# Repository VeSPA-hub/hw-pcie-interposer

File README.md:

# PCIe interposer

Board design files of the VeSPA PCIe interposer

	Note: This design was performed in KiCad nightly , you will need a Nightly build to open and edit these source files.

# Status

This version has not been fully tested yet.

# What it is

This board can tap PCIe signals (RX, TX and clock) at Gen2 speed.
Signals go to a redriver before they are sent to the actual analyzer using a DisplayPort cable.

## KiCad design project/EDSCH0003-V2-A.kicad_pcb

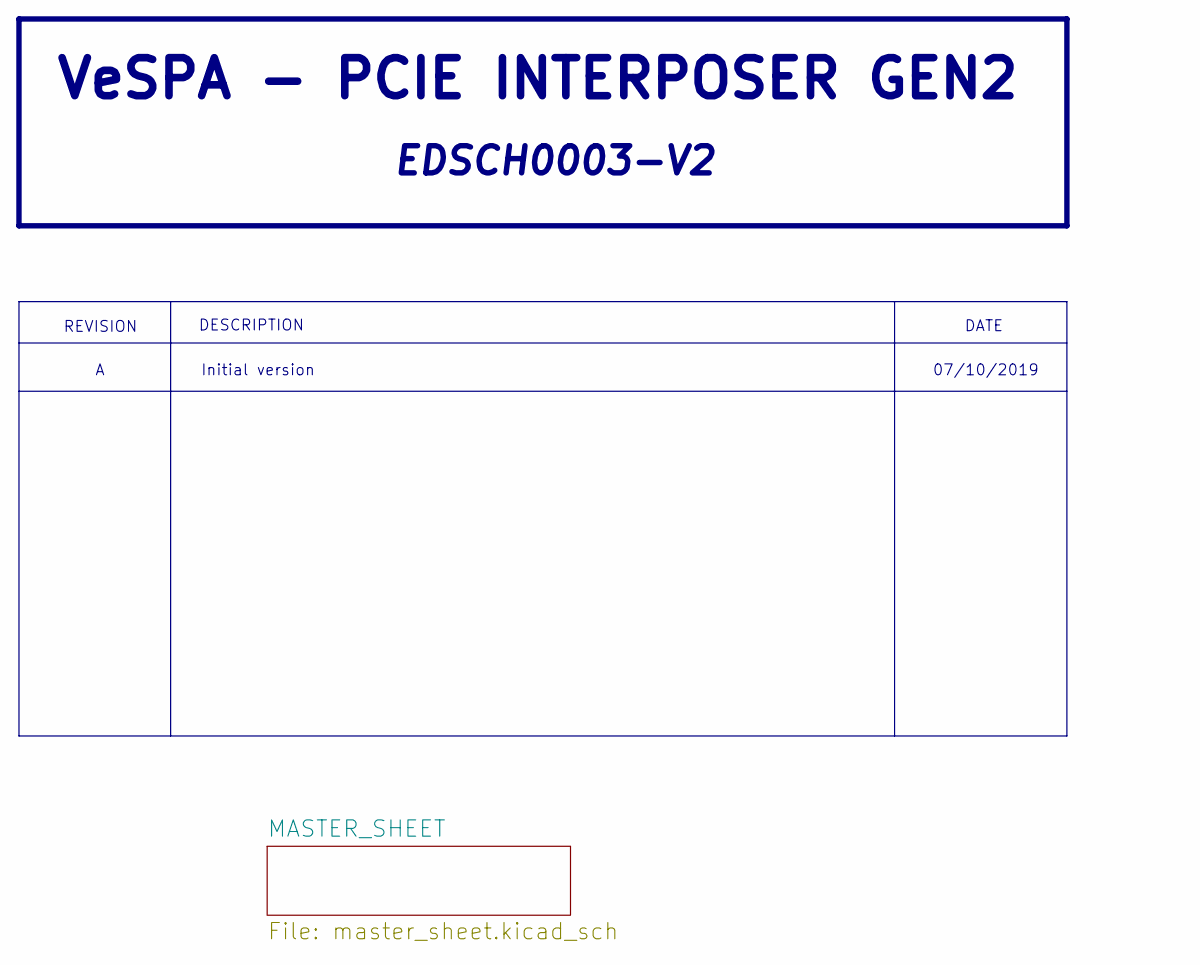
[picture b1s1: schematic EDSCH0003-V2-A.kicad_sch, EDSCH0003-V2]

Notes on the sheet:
VeSPA - PCIE INTERPOSER GEN2
REVISION
DESCRIPTION
Initial version
EDSCH0003-V2
DATE
07/10/2019

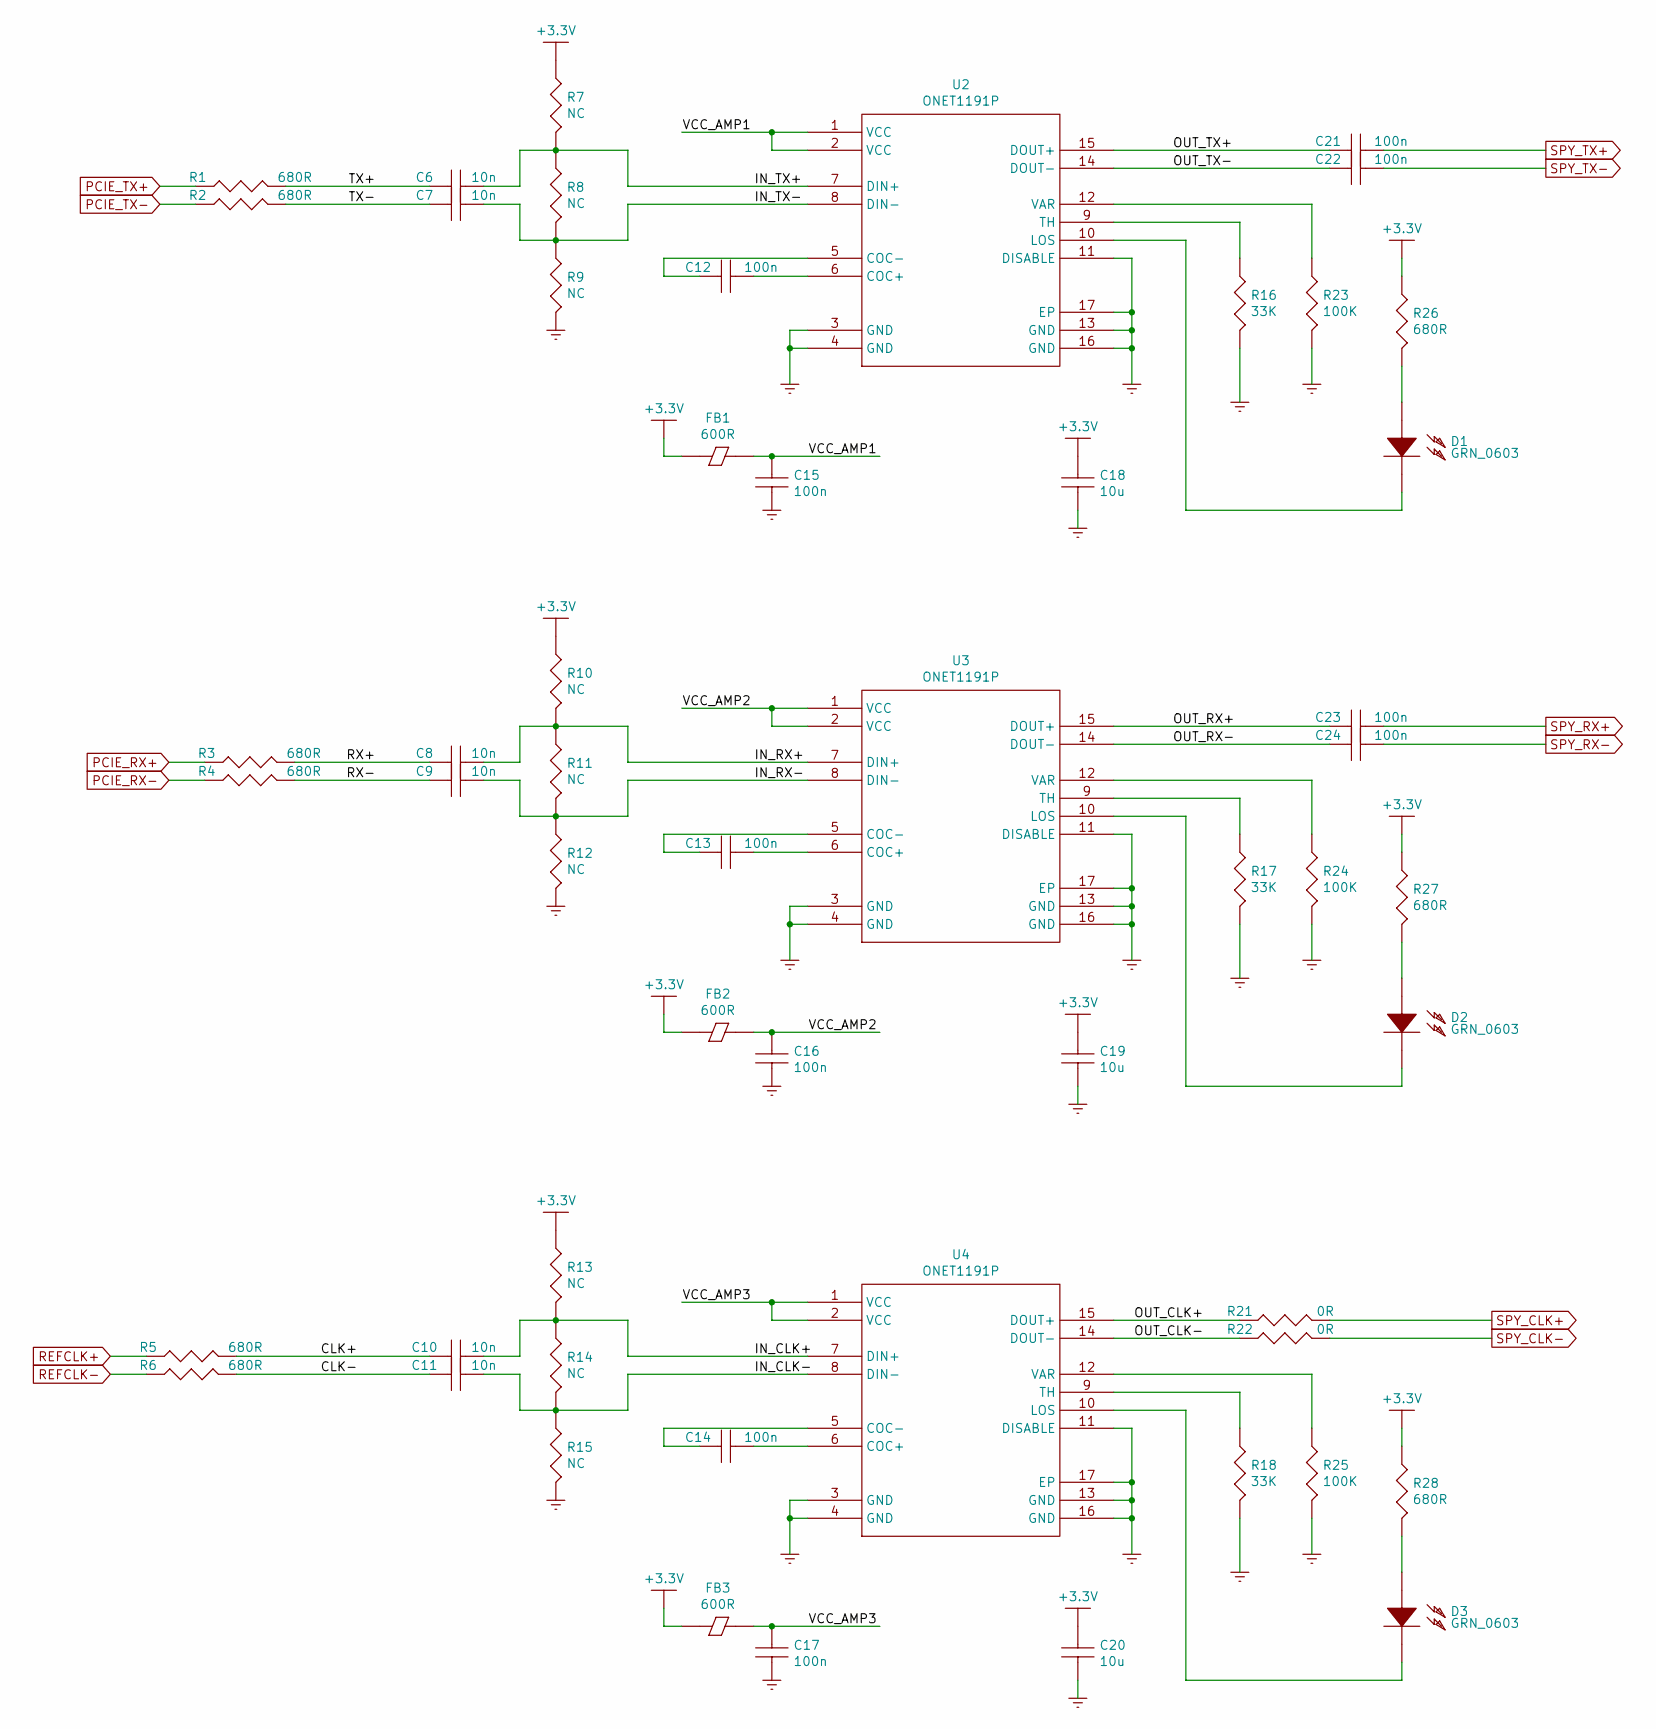
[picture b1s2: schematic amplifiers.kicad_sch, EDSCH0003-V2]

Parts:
C6, C7, C8, C9, C10, C11: C10N_0402; r_smt0402_ref
C12, C13, C14, C15, C16, C17, C21, C22, C23, C24: C100N_16V_0402; r_smt0402_ref
C18, C19, C20: C10U_50V_1206; c_smt1206_ref
D1, D2, D3: LED_GRN_0603; LED_0603_1608Metric_Castellated
FB1, FB2, FB3: FR_600R_0.2A_0402; r_smt0402_ref
R1, R2, R3, R4, R5, R6, R26, R27, R28: R680R_1%_0603; r_smt0603_ref
R7, R8, R9, R10, R11, R12, R13, R14, R15: R_NC_0402; r_smt0402_ref
R16, R17, R18: R33K_1%_0402; r_smt0402_ref
R21, R22: R0R_5%_0402; r_smt0402_ref
R23, R24, R25: R100K_1%_0402; r_smt0402_ref
U2, U3, U4: ONET1191P; QFN-16-1EP_3x3mm_P0.5mm_EP1.7x1.7mm

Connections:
+3.3V: C18.1, C19.1, C20.1, FB1.1, FB2.1, FB3.1, R7.1, R10.1, R13.1, R26.1, R27.1, R28.1; also elsewhere on the board
/MASTER_SHEET/AMPLIFIERS/CLK+: C10.1, R5.2
/MASTER_SHEET/AMPLIFIERS/CLK-: C11.1, R6.2
/MASTER_SHEET/AMPLIFIERS/IN_CLK+: C10.2, R13.2, R14.1, U4.7 (DIN+)
/MASTER_SHEET/AMPLIFIERS/IN_CLK-: C11.2, R14.2, R15.1, U4.8 (DIN-)
/MASTER_SHEET/AMPLIFIERS/IN_RX+: C8.2, R10.2, R11.1, U3.7 (DIN+)
/MASTER_SHEET/AMPLIFIERS/IN_RX-: C9.2, R11.2, R12.1, U3.8 (DIN-)
/MASTER_SHEET/AMPLIFIERS/IN_TX+: C6.2, R7.2, R8.1, U2.7 (DIN+)
/MASTER_SHEET/AMPLIFIERS/IN_TX-: C7.2, R8.2, R9.1, U2.8 (DIN-)
/MASTER_SHEET/AMPLIFIERS/OUT_CLK+: R21.1, U4.15 (DOUT+)
/MASTER_SHEET/AMPLIFIERS/OUT_CLK-: R22.1, U4.14 (DOUT-)
/MASTER_SHEET/AMPLIFIERS/OUT_RX+: C23.1, U3.15 (DOUT+)
/MASTER_SHEET/AMPLIFIERS/OUT_RX-: C24.1, U3.14 (DOUT-)
/MASTER_SHEET/AMPLIFIERS/OUT_TX+: C21.1, U2.15 (DOUT+)
/MASTER_SHEET/AMPLIFIERS/OUT_TX-: C22.1, U2.14 (DOUT-)
/MASTER_SHEET/AMPLIFIERS/RX+: C8.1, R3.2
/MASTER_SHEET/AMPLIFIERS/RX-: C9.1, R4.2
/MASTER_SHEET/AMPLIFIERS/TX+: C6.1, R1.2
/MASTER_SHEET/AMPLIFIERS/TX-: C7.1, R2.2
/MASTER_SHEET/AMPLIFIERS/VCC_AMP1: C15.1, FB1.2, U2.1 (VCC), U2.2 (VCC)
/MASTER_SHEET/AMPLIFIERS/VCC_AMP2: C16.1, FB2.2, U3.1 (VCC), U3.2 (VCC)
/MASTER_SHEET/AMPLIFIERS/VCC_AMP3: C17.1, FB3.2, U4.1 (VCC), U4.2 (VCC)
GND: C15.2, C16.2, C17.2, C18.2, C19.2, C20.2, R9.2, R12.2, R15.2, R16.2, R17.2, R18.2, R23.2, R24.2, R25.2, U2.3 (GND), U2.4 (GND), U2.11 (DISABLE), U2.13 (GND), U2.16 (GND), U2.17 (EP), U3.3 (GND), U3.4 (GND), U3.11 (DISABLE), U3.13 (GND), U3.16 (GND), U3.17 (EP), U4.3 (GND), U4.4 (GND), U4.11 (DISABLE), U4.13 (GND), U4.16 (GND), U4.17 (EP); also elsewhere on the board
unnamed: C12.1, U2.5 (COC-)
unnamed: C12.2, U2.6 (COC+)
unnamed: C13.1, U3.5 (COC-)
unnamed: C13.2, U3.6 (COC+)
unnamed: C14.1, U4.5 (COC-)
unnamed: C14.2, U4.6 (COC+)
unnamed: D1.1 (A), R26.2
unnamed: D1.2 (K), U2.10 (LOS)
unnamed: D2.1 (A), R27.2
unnamed: D2.2 (K), U3.10 (LOS)
unnamed: D3.1 (A), R28.2
unnamed: D3.2 (K), U4.10 (LOS)
unnamed: R16.1, U2.9 (TH)
unnamed: R17.1, U3.9 (TH)
unnamed: R18.1, U4.9 (TH)
unnamed: R23.1, U2.12 (VAR)
unnamed: R24.1, U3.12 (VAR)
unnamed: R25.1, U4.12 (VAR)
PCIE_RX+: R3.1; also elsewhere on the board
PCIE_RX-: R4.1; also elsewhere on the board
PCIE_TX+: R1.1; also elsewhere on the board
PCIE_TX-: R2.1; also elsewhere on the board
REFCLK+: R5.1; also elsewhere on the board
REFCLK-: R6.1; also elsewhere on the board
SPY_CLK+: R21.2; also elsewhere on the board
SPY_CLK-: R22.2; also elsewhere on the board
SPY_RX+: C23.2; also elsewhere on the board
SPY_RX-: C24.2; also elsewhere on the board
SPY_TX+: C21.2; also elsewhere on the board
SPY_TX-: C22.2; also elsewhere on the board

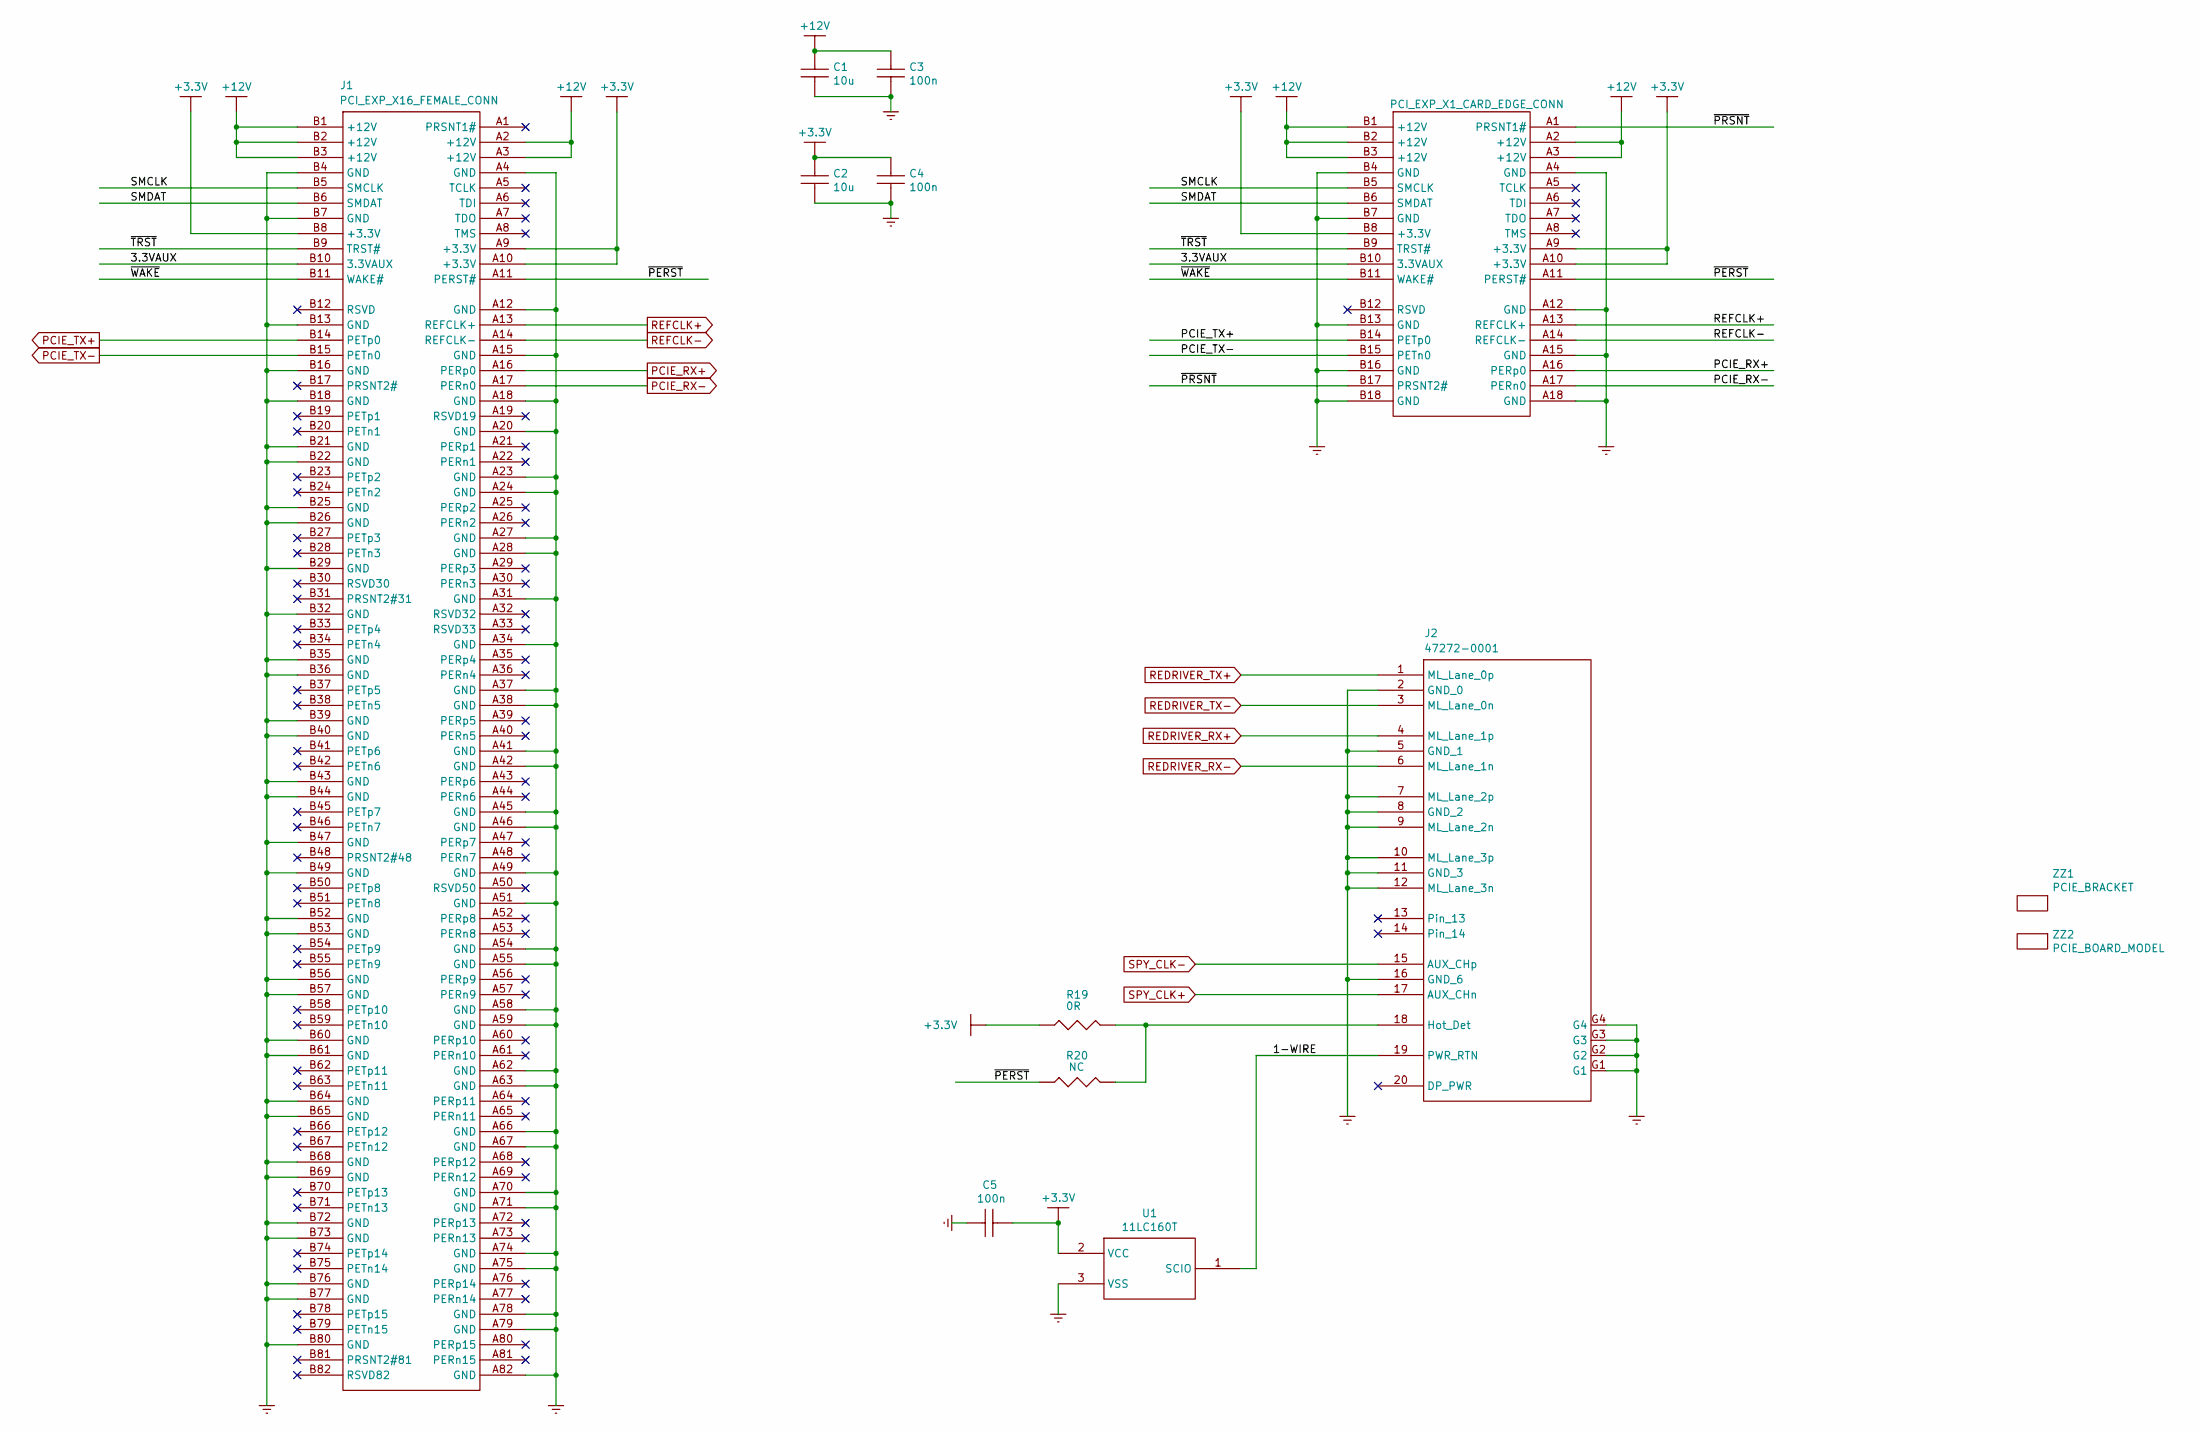
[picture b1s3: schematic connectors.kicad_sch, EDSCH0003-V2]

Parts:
C1, C2: C10U_50V_1206; c_smt1206_ref
C3, C4, C5: C100N_16V_0402; r_smt0402_ref
J1: PCIEXP_X16_EDGE_MOUNT_CONN; samtec_pcie_ems2
J2: DISPLAY_PORT; molex_display_port
P1: PCIEXP_X1_CARD_EDGE; BUS_PCIexpress_x1
R19: R0R_5%_0402; r_smt0402_ref
R20: R_NC_0402; r_smt0402_ref
U1: EEPROM_1WIRE_2Kx8_11LC160T; SOT-23
ZZ1: PCIE_BRACKET; pcie_bracket
ZZ2: PCIE_BOARD_MODEL; BUS_PCIexpress

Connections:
+3.3V: C2.1, C4.1, C5.2, J1.A9 (+3.3V), J1.A10 (+3.3V), J1.B8 (+3.3V), P1.A9 (+3.3V), P1.A10 (+3.3V), P1.B8 (+3.3V), R19.1, U1.2 (VCC); also elsewhere on the board
+12V: C1.1, C3.1, J1.A2 (+12V), J1.A3 (+12V), J1.B1 (+12V), J1.B2 (+12V), J1.B3 (+12V), P1.A2 (+12V), P1.A3 (+12V), P1.B1 (+12V), P1.B2 (+12V), P1.B3 (+12V)
/MASTER_SHEET/CONNECTORS/1-WIRE: J2.19 (PWR_RTN), U1.1 (SCIO)
/MASTER_SHEET/CONNECTORS/3.3VAUX: J1.B10 (3.3VAUX), P1.B10 (3.3VAUX)
/MASTER_SHEET/CONNECTORS/SMCLK: J1.B5 (SMCLK), P1.B5 (SMCLK)
/MASTER_SHEET/CONNECTORS/SMDAT: J1.B6 (SMDAT), P1.B6 (SMDAT)
/MASTER_SHEET/CONNECTORS/~PERST: J1.A11 (PERST#), P1.A11 (PERST#), R20.1
/MASTER_SHEET/CONNECTORS/~PRSNT: P1.A1 (PRSNT1#), P1.B17 (PRSNT2#)
/MASTER_SHEET/CONNECTORS/~TRST: J1.B9 (TRST#), P1.B9 (TRST#)
/MASTER_SHEET/CONNECTORS/~WAKE: J1.B11 (WAKE#), P1.B11 (WAKE#)
GND: C1.2, C2.2, C3.2, C4.2, C5.1, J1.A4 (GND), J1.A12 (GND), J1.A15 (GND), J1.A18 (GND), J1.A20 (GND), J1.A23 (GND), J1.A24 (GND), J1.A27 (GND), J1.A28 (GND), J1.A31 (GND), J1.A34 (GND), J1.A37 (GND), J1.A38 (GND), J1.A41 (GND), J1.A42 (GND), J1.A45 (GND), J1.A46 (GND), J1.A49 (GND), J1.A51 (GND), J1.A54 (GND), J1.A55 (GND), J1.A58 (GND), J1.A59 (GND), J1.A62 (GND), J1.A63 (GND), J1.A66 (GND), J1.A67 (GND), J1.A70 (GND), J1.A71 (GND), J1.A74 (GND), J1.A75 (GND), J1.A78 (GND), J1.A79 (GND), J1.A82 (GND), J1.B4 (GND), J1.B7 (GND), J1.B13 (GND), J1.B16 (GND), J1.B18 (GND), J1.B21 (GND), J1.B22 (GND), J1.B25 (GND), J1.B26 (GND), J1.B29 (GND), J1.B32 (GND), J1.B35 (GND), J1.B36 (GND), J1.B39 (GND), J1.B40 (GND), J1.B43 (GND), J1.B44 (GND), J1.B47 (GND), J1.B49 (GND), J1.B52 (GND), J1.B53 (GND), J1.B56 (GND), J1.B57 (GND), J1.B60 (GND), J1.B61 (GND), J1.B64 (GND), J1.B65 (GND), J1.B68 (GND), J1.B69 (GND), J1.B72 (GND), J1.B73 (GND), J1.B76 (GND), J1.B77 (GND), J1.B80 (GND), J2.2 (GND_0), J2.5 (GND_1), J2.7 (ML_Lane_2p), J2.8 (GND_2), J2.9 (ML_Lane_2n), J2.10 (ML_Lane_3p), J2.11 (GND_3), J2.12 (ML_Lane_3n), J2.16 (GND_6), J2.G1, J2.G2, J2.G3, J2.G4, P1.A4 (GND), P1.A12 (GND), P1.A15 (GND), P1.A18 (GND), P1.B4 (GND), P1.B7 (GND), P1.B13 (GND), P1.B16 (GND), P1.B18 (GND), U1.3 (VSS); also elsewhere on the board
unnamed: J2.18 (Hot_Det), R19.2, R20.2
PCIE_RX+: J1.A16 (PERp0), P1.A16 (PERp0); also elsewhere on the board
PCIE_RX-: J1.A17 (PERn0), P1.A17 (PERn0); also elsewhere on the board
PCIE_TX+: J1.B14 (PETp0), P1.B14 (PETp0); also elsewhere on the board
PCIE_TX-: J1.B15 (PETn0), P1.B15 (PETn0); also elsewhere on the board
REDRIVER_RX+: J2.4 (ML_Lane_1p); also elsewhere on the board
REDRIVER_RX-: J2.6 (ML_Lane_1n); also elsewhere on the board
REDRIVER_TX+: J2.1 (ML_Lane_0p); also elsewhere on the board
REDRIVER_TX-: J2.3 (ML_Lane_0n); also elsewhere on the board
REFCLK+: J1.A13 (REFCLK+), P1.A13 (REFCLK+); also elsewhere on the board
REFCLK-: J1.A14 (REFCLK-), P1.A14 (REFCLK-); also elsewhere on the board
SPY_CLK+: J2.17 (AUX_CHn); also elsewhere on the board
SPY_CLK-: J2.15 (AUX_CHp); also elsewhere on the board

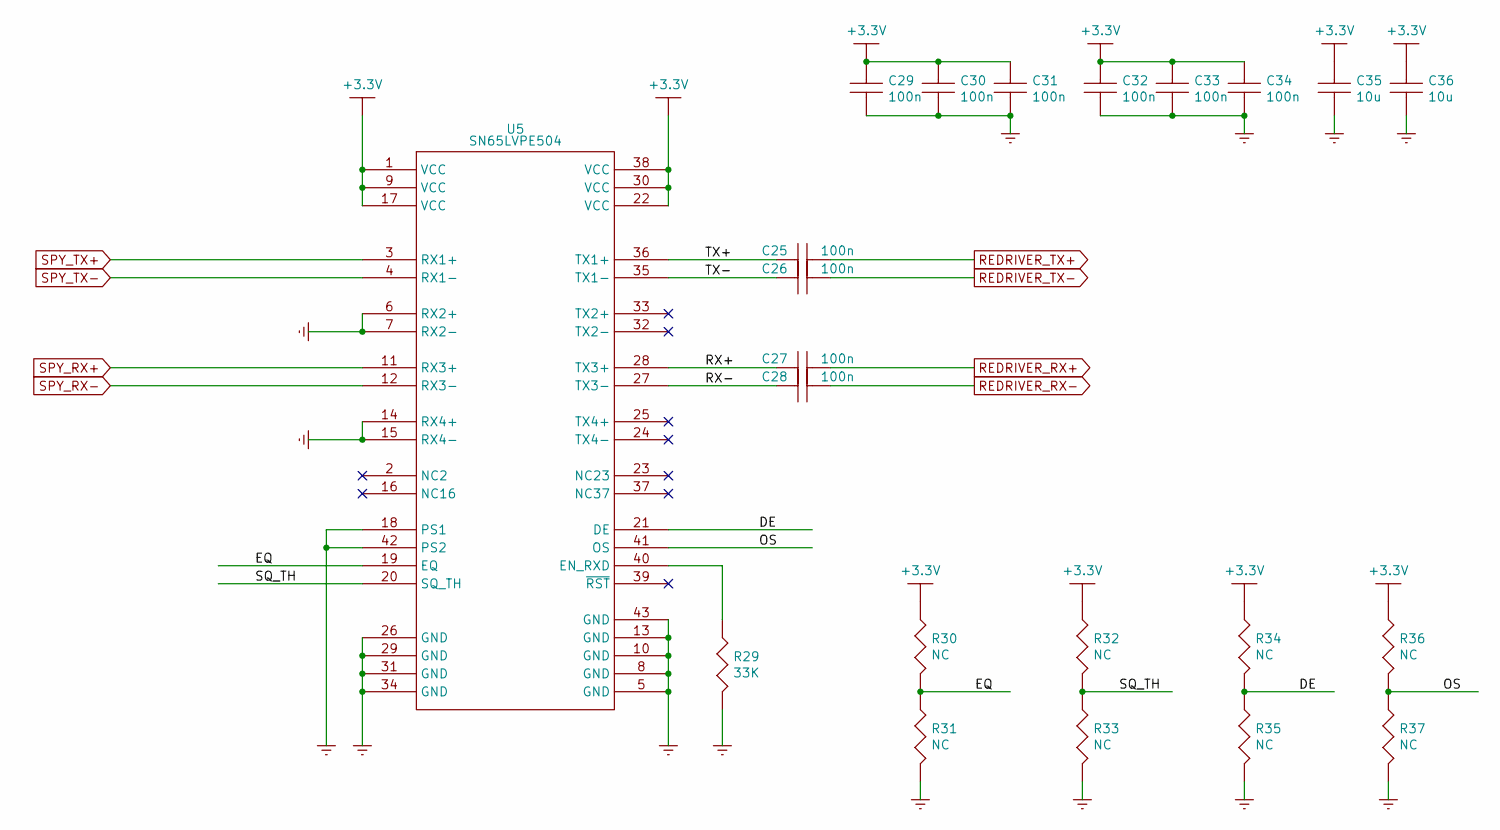
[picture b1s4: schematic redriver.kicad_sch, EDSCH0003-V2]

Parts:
C25, C26, C27, C28, C29, C30, C31, C32, C33, C34: C100N_16V_0402; r_smt0402_ref
C35, C36: C10U_50V_1206; c_smt1206_ref
R29: R33K_1%_0402; r_smt0402_ref
R30, R31, R32, R33, R34, R35, R36, R37: R_NC_0402; r_smt0402_ref
U5: PCIe_HALF_x4_Gen2_SN65LVPE504; pwqfn-n42

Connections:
+3.3V: C29.1, C30.1, C31.1, C32.1, C33.1, C34.1, C35.1, C36.1, R30.1, R32.1, R34.1, R36.1, U5.1 (VCC), U5.9 (VCC), U5.17 (VCC), U5.22 (VCC), U5.30 (VCC), U5.38 (VCC); also elsewhere on the board
/MASTER_SHEET/REDRIVER/DE: R34.2, R35.1, U5.21 (DE)
/MASTER_SHEET/REDRIVER/EQ: R30.2, R31.1, U5.19 (EQ)
/MASTER_SHEET/REDRIVER/OS: R36.2, R37.1, U5.41 (OS)
/MASTER_SHEET/REDRIVER/RX+: C27.1, U5.28 (TX3+)
/MASTER_SHEET/REDRIVER/RX-: C28.1, U5.27 (TX3-)
/MASTER_SHEET/REDRIVER/SQ_TH: R32.2, R33.1, U5.20 (SQ_TH)
/MASTER_SHEET/REDRIVER/TX+: C25.1, U5.36 (TX1+)
/MASTER_SHEET/REDRIVER/TX-: C26.1, U5.35 (TX1-)
GND: C29.2, C30.2, C31.2, C32.2, C33.2, C34.2, C35.2, C36.2, R29.2, R31.2, R33.2, R35.2, R37.2, U5.5 (GND), U5.6 (RX2+), U5.7 (RX2-), U5.8 (GND), U5.10 (GND), U5.13 (GND), U5.14 (RX4+), U5.15 (RX4-), U5.18 (PS1), U5.26 (GND), U5.29 (GND), U5.31 (GND), U5.34 (GND), U5.42 (PS2), U5.43 (GND); also elsewhere on the board
unnamed: R29.1, U5.40 (EN_RXD)
REDRIVER_RX+: C27.2; also elsewhere on the board
REDRIVER_RX-: C28.2; also elsewhere on the board
REDRIVER_TX+: C25.2; also elsewhere on the board
REDRIVER_TX-: C26.2; also elsewhere on the board
SPY_RX+: U5.11 (RX3+); also elsewhere on the board
SPY_RX-: U5.12 (RX3-); also elsewhere on the board
SPY_TX+: U5.3 (RX1+); also elsewhere on the board
SPY_TX-: U5.4 (RX1-); also elsewhere on the board

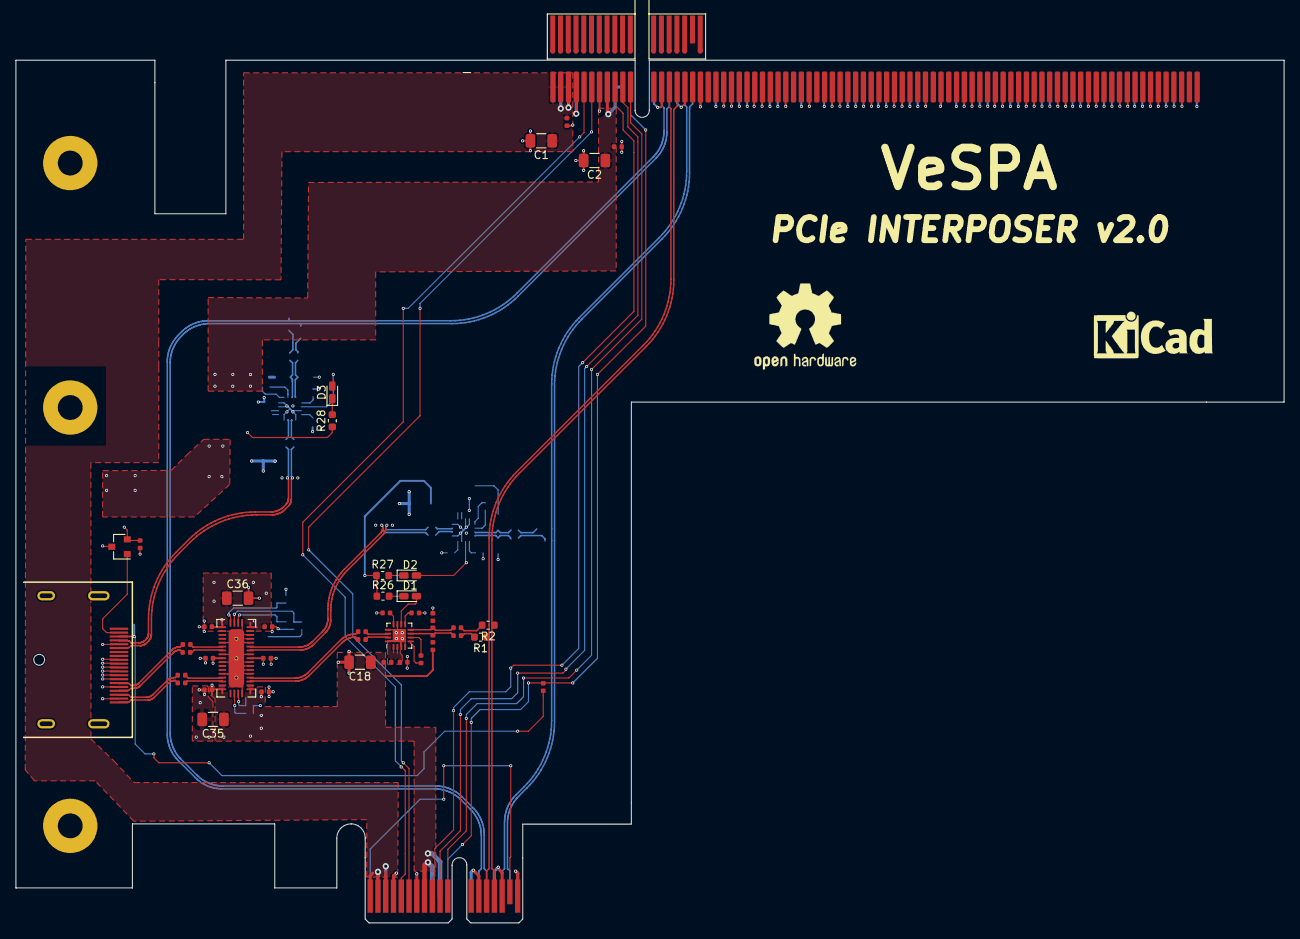
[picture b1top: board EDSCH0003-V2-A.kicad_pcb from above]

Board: 4 copper layers, 163.4 x 111.2 mm, 89 parts (0 on the bottom side), 76 nets.

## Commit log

2020-07-30 Initial release
2020-08-21 Clean-up files
2020-08-21 Add gerber files
